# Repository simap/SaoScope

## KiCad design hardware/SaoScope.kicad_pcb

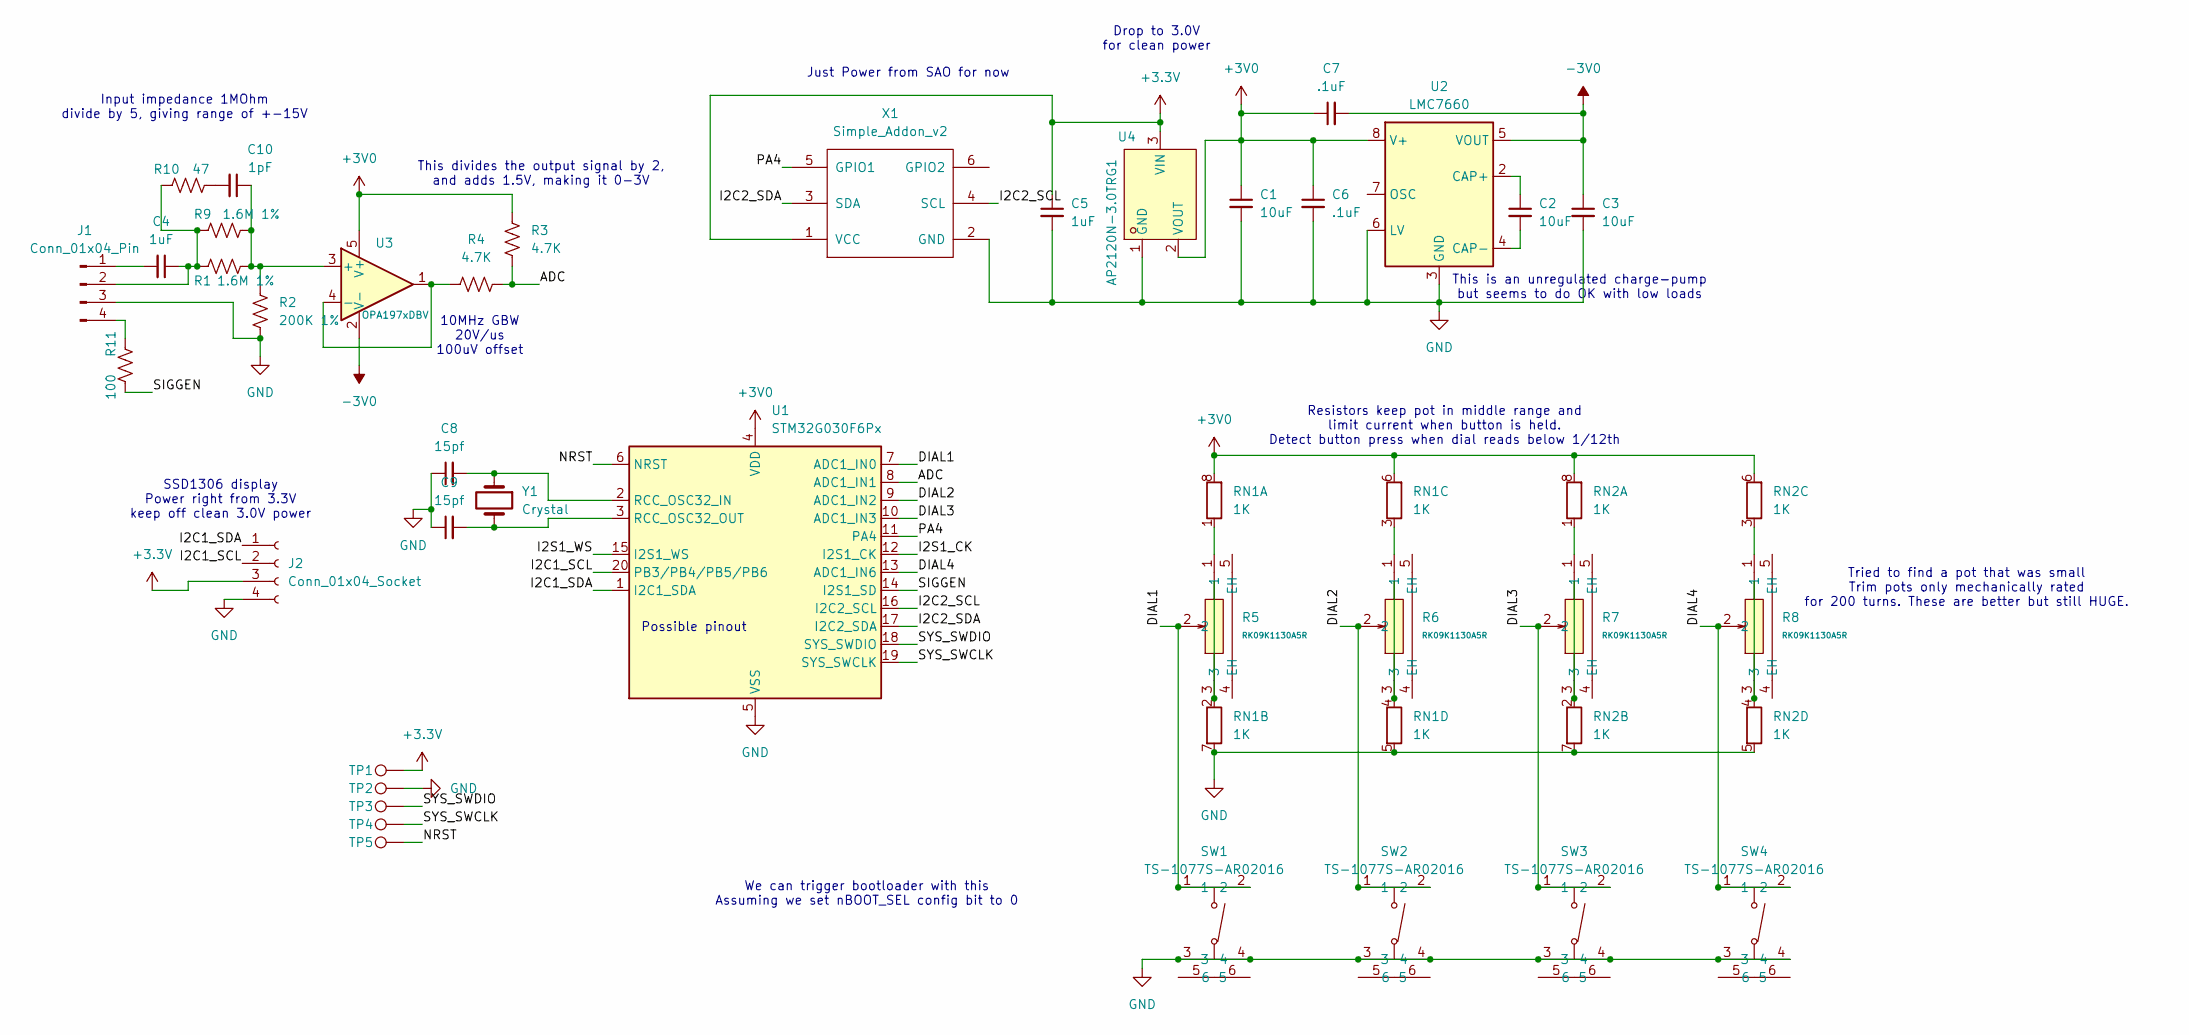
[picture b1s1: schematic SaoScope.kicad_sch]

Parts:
C1, C2, C3: 10uF; C_0805_2012Metric
C4, C5: 1uF; C_0603_1608Metric
C6, C7: .1uF; C_0402_1005Metric
C8, C9: 15pf; C_0402_1005Metric
C10: 1pF; C_0402_1005Metric
J1: Conn_01x04_Pin; PinHeader_1x04_P2.54mm_Vertical
J2: Conn_01x04_Socket; ssd1306_module
R1, R9: 1.6M 1%; R_0402_1005Metric; LCSC Part C172161
R2: 200K 1%; R_0402_1005Metric; LCSC Part C25764
R3, R4: 4.7K; R_0402_1005Metric
R5, R6, R7, R8: RK09K1130A5R; RES-ADJ-TH_RK09K1130A5R; LCSC Part C209779
R10: 47; R_0402_1005Metric; LCSC Part C172161
R11: 100; R_0402_1005Metric; LCSC Part C172161
RN1, RN2: 1K; R_Array_Convex_4x0402; LCSC Part C2769475
SW1, SW2, SW3, SW4: TS-1077S-AR02016; KEY-SMD_4P-L3.1-W3.1-P2.00-LS4.0; LCSC Part C720462
TP1, TP2, TP3, TP4, TP5: TestPoint; TestPoint_Pad_1.5x1.5mm
U1: STM32G030F6Px; TSSOP-20_4.4x6.5mm_P0.65mm
U2: LMC7660; SOP-8_3.9x4.9mm_P1.27mm
U3: OPA197xDBV; SOT-23-5
U4: AP2120N-3.0TRG1; SOT-23-3_L2.9-W1.3-P1.90-LS2.4-BR; LCSC Part C460318
X1: Simple_Addon_v2; Simple_Addon_v2-SAO-2x3
Y1: Crystal; Crystal_SMD_3215-2Pin_3.2x1.5mm; LCSC Part C5213671

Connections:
+3.3V: C5.1, J2.3, TP1.1, U4.3 (VIN), X1.1 (VCC)
+3V0: C1.1, C6.1, C7.1, R3.2, RN1.6 (R3.2), RN1.8 (R1.2), RN2.6 (R3.2), RN2.8 (R1.2), U1.4 (VDD), U2.8 (V+), U3.5 (V+), U4.2 (VOUT)
-3V0: C3.1, C7.2, U2.5 (VOUT), U3.2 (V-)
/ADC: R3.1, R4.2, U1.8 (ADC1_IN1)
/DIAL1: R5.2, SW1.1, SW1.2, U1.7 (ADC1_IN0)
/DIAL2: R6.2, SW2.1, SW2.2, U1.9 (ADC1_IN2)
/DIAL3: R7.2, SW3.1, SW3.2, U1.10 (ADC1_IN3)
/DIAL4: R8.2, SW4.1, SW4.2, U1.13 (ADC1_IN6)
/I2C1_SCL: J2.2, U1.20 (PB3/PB4/PB5/PB6)
/I2C1_SDA: J2.1, U1.1 (I2C1_SDA)
/I2C2_SCL: U1.16 (I2C2_SCL), X1.4 (SCL)
/I2C2_SDA: U1.17 (I2C2_SDA), X1.3 (SDA)
/I2S1_CK: U1.12 (I2S1_CK)
/I2S1_WS: U1.15 (I2S1_WS)
/NRST: TP5.1, U1.6 (NRST)
/PA4: U1.11 (PA4), X1.5 (GPIO1)
/SIGGEN: R11.2, U1.14 (I2S1_SD)
/SYS_SWCLK: TP4.1, U1.19 (SYS_SWCLK)
/SYS_SWDIO: TP3.1, U1.18 (SYS_SWDIO)
GND: C1.2, C3.2, C5.2, C6.2, C8.1, C9.1, J1.3, J2.4, R2.2, RN1.5 (R4.2), RN1.7 (R2.2), RN2.5 (R4.2), RN2.7 (R2.2), SW1.3, SW1.4, SW2.3, SW2.4, SW3.3, SW3.4, SW4.3, SW4.4, TP2.1, U1.5 (VSS), U2.3 (GND), U2.6 (LV), U4.1 (GND), X1.2 (GND)
unnamed: C10.2, R10.2
unnamed: C4.2, J1.1
unnamed: C4.1, J1.2, R1.1, R9.1, R10.1
unnamed: J1.4, R11.1
unnamed: R5.1, RN1.1 (R1.1)
unnamed: R5.3, RN1.2 (R2.1)
unnamed: R6.1, RN1.3 (R3.1)
unnamed: R6.3, RN1.4 (R4.1)
unnamed: R7.1, RN2.1 (R1.1)
unnamed: R7.3, RN2.2 (R2.1)
unnamed: R8.1, RN2.3 (R3.1)
unnamed: R8.3, RN2.4 (R4.1)
unnamed: C8.2, U1.2 (RCC_OSC32_IN), Y1.1
unnamed: C9.2, U1.3 (RCC_OSC32_OUT), Y1.2
unnamed: C2.1, U2.2 (CAP+)
unnamed: C2.2, U2.4 (CAP-)
unnamed: C10.1, R1.2, R2.1, R9.2, U3.3 (+)
unnamed: R4.1, U3.1, U3.4 (-)

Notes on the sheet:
We can trigger bootloader with this Assuming we set nBOOT_SEL config bit to 0
Resistors keep pot in middle range and limit current when button is held. Detect button press when dial reads below 1/12th
This divides the output signal by 2, and adds 1.5V, making it 0-3V
SSD1306 display Power right from 3.3V keep off clean 3.0V power
Just Power from SAO for now
Tried to find a pot that was small Trim pots only mechanically rated for 200 turns. These are better but still HUGE.
Drop to 3.0V for clean power
This is an unregulated charge-pump but seems to do OK with low loads
Possible pinout
Input impedance 1MOhm divide by 5, giving range of +-15V
10MHz GBW 20V/us 100uV offset

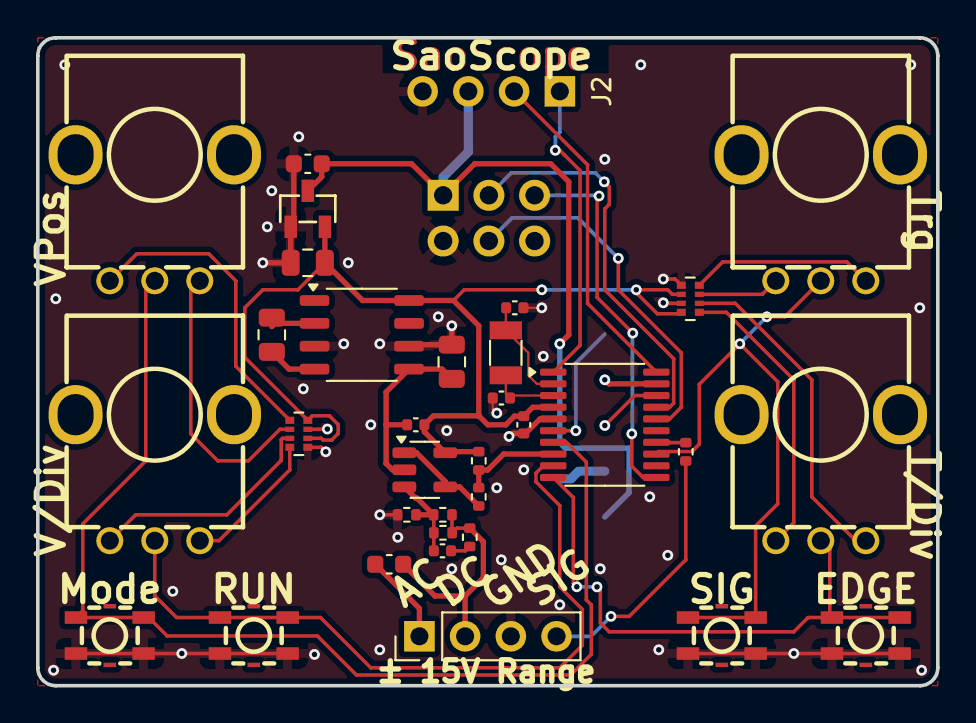
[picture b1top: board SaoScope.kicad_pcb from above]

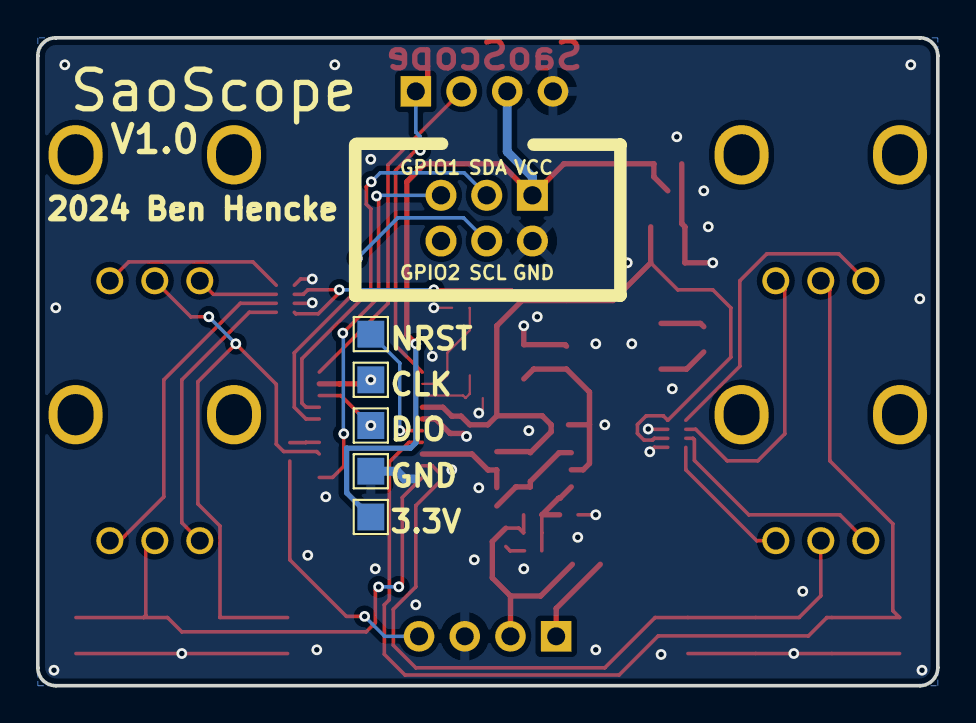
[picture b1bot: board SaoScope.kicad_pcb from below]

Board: 2 copper layers, 50.0 x 36.0 mm, 40 parts (5 on the bottom side), 36 nets.

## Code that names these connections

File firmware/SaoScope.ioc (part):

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Mcu.Name=STM32G030F6Px
Mcu.Package=TSSOP20
Mcu.UserName=STM32G030F6Px
PA0.GPIOParameters=GPIO_Label
PA0.GPIO_Label=DIAL1
PA0.Mode=IN0
PA0.Signal=ADC1_IN0
PA1.GPIOParameters=GPIO_Label
PA1.GPIO_Label=SCOPE
PA1.Mode=IN1
PA1.Signal=ADC1_IN1
PA11\ [PA9].Mode=I2C
PA11\ [PA9].Signal=I2C2_SCL
PA12\ [PA10].Mode=I2C
PA12\ [PA10].Signal=I2C2_SDA
PA13.Mode=Serial_Wire
PA13.Signal=SYS_SWDIO
PA14-BOOT0.Mode=Serial_Wire
PA14-BOOT0.Signal=SYS_SWCLK
PA14-BOOT0__PA15.StandardMode=true
PA2.GPIOParameters=GPIO_Label
PA2.GPIO_Label=DIAL2
PA2.Mode=IN2
PA2.Signal=ADC1_IN2
PA3.GPIOParameters=GPIO_Label
PA3.GPIO_Label=DIAL3
PA3.Mode=IN3
PA3.Signal=ADC1_IN3
PA4.Signal=GPIO_Input
PA5.Mode=Half_Duplex_Master
PA5.Signal=I2S1_CK
PA6.GPIOParameters=GPIO_Label
PA6.GPIO_Label=DIAL4
PA6.Mode=IN6
PA6.Signal=ADC1_IN6
PA7.GPIOParameters=GPIO_Speed
PA7.GPIO_Speed=GPIO_SPEED_FREQ_VERY_HIGH
PA7.Signal=SharedStack_PA7
PA7.Stacked=true
PB0.Mode=Half_Duplex_Master
PB0.Signal=I2S1_WS
PB0__PB1__PB2__PA8.StandardMode=true
PB3__PB4__PB5__PB6.StandardMode=true
PB6.GPIOParameters=GPIO_FM6,GPIO_Speed
PB6.GPIO_FM6=SYSCFG_FASTMODEPLUS_PB6
PB6.GPIO_Speed=GPIO_SPEED_FREQ_VERY_HIGH
PB6.Mode=I2C
PB6.Signal=I2C1_SCL
PB7.GPIOParameters=GPIO_Speed,GPIO_FM7
PB7.GPIO_FM7=SYSCFG_FASTMODEPLUS_PB7
PB7.GPIO_Speed=GPIO_SPEED_FREQ_VERY_HIGH
PB7.Mode=I2C
PB7.Signal=I2C1_SDA
PB7__PB8.StandardMode=true
PC14-OSC32_IN\ (PC14).Mode=LSE-External-Oscillator
PC14-OSC32_IN\ (PC14).Signal=RCC_OSC32_IN
PC14-OSC32_IN\ (PC14)__PB9.StandardMode=true
PC15-OSC32_OUT\ (PC15).Mode=LSE-External-Oscillator
PC15-OSC32_OUT\ (PC15).Signal=RCC_OSC32_OUT
RCC.HSE_VALUE=8000000
RCC.SYSCLKFreq_VALUE=56000000
RCC.SYSCLKSource=RCC_SYSCLKSOURCE_PLLCLK
board=custom

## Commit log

2024-09-26 initial
2024-09-26 placeholder unlicense until I figure out what to do with it
2024-09-26 gitignore
2024-09-26 wire up pots and buttons, comments
2024-09-27 make fit in 50mm
2024-09-27 basic rev
2024-09-27 more graphics/text
2024-09-27 bigger holes, rounder edges
2024-09-27 blue, text
2024-09-27 split faceplate to another file
2024-10-07 switch 800k with two 1.6M resistors
2024-10-12 bring in i2c lines from sao, a gpio, and run a sig gen line out. rework button labels.
2024-10-23 add basic POC code - scan fast and draw on screen
    copied over from penscope project. lots of quick hacks, proof of concept.
    some files, like scope.c, are more idea than working code.
2024-10-23 license clarifications
2024-10-23 cleanup, doc tim17
2024-10-24 fix part number oops
2024-10-25 scans buttons and dials now
    move adc stuff to adcmanager, add dial helper
    scope sampling is kinda wonky since it doesn't pause sampling to capture a waveform, but will fix that soon
2024-10-26 wire in some super basic support for vpos, vdiv, tdiv, and run btn
2024-10-31 WIP getting closer to usable, a bit unstable, but most buttons and dials do stuff
    continuous scan works
    trigger dial works with software edge detect
    trigger using adc watchdogs still WIP.
    a bit messy, will need cleanup
2024-10-31 has scope-like t/div increments
    fixed a few other issues.
    disabled sample speeds faster than 1.75msps until time can be spent making things work better when the sample bits change.
    graph can be scaled independent of sample snapshot. so you can stop the scope and zoom in/out, and get sane scope-like t/div increments.
    running the scope starts sampling at a rate that gets at least one sample per pixel if possible.
    normal and single mode still not working, disabled for now.
    better trigger threshold control
2024-11-02 signal gen, 20-500khz, scope modes working
2024-11-02 show sig gen message, fine tune edge refiner
2024-11-02 fix issue when changing scope mode mid scan, vdiv dots, ui cleanup
